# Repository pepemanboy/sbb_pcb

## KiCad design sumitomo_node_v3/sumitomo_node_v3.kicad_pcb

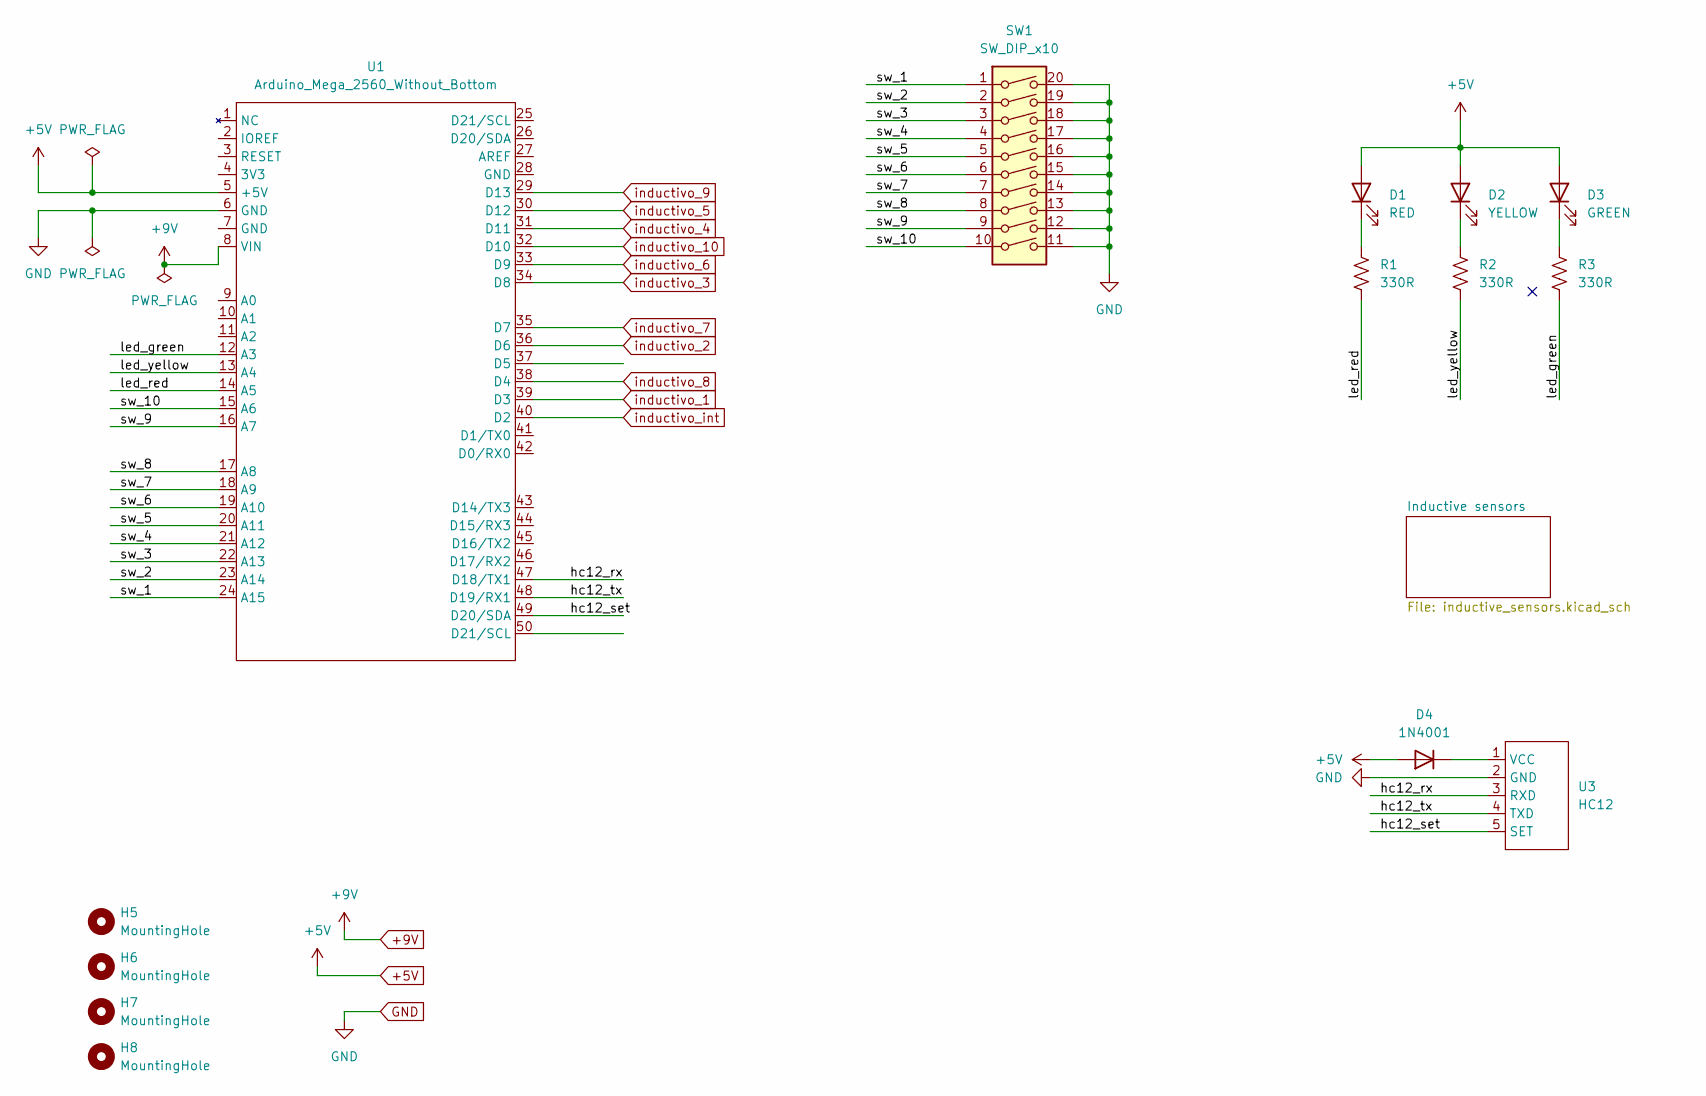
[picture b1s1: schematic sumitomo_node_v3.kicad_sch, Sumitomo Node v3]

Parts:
D1: RED; LED_D5.0mm
D2: YELLOW; LED_D5.0mm
D3: GREEN; LED_D5.0mm
D4: 1N4001; D_DO-41_SOD81_P10.16mm_Horizontal
H5, H6, H7, H8: MountingHole; MountingHole_3.2mm_M3_ISO7380
R1, R2, R3: 330R; R_Axial_DIN0207_L6.3mm_D2.5mm_P10.16mm_Horizontal
SW1: SW_DIP_x10; SW_DIP_SPSTx10_Slide_9.78x27.58mm_W7.62mm_P2.54mm
U1: Arduino_Mega_2560_Without_Bottom
U3: HC12; HC12_RF_Module

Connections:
+5V: D1.2 (A), D2.2 (A), D3.2 (A), D4.2 (A), U1.5 (+5V); also elsewhere on the board
+9V: U1.8 (VIN); also elsewhere on the board
/hc12_rx: U1.47 (D18/TX1), U3.3 (RXD)
/hc12_set: U1.49 (D20/SDA), U3.5 (SET)
/hc12_tx: U1.48 (D19/RX1), U3.4 (TXD)
/led_green: R3.1, U1.12 (A3)
/led_red: R1.1, U1.14 (A5)
/led_yellow: R2.1, U1.13 (A4)
/sw_1: SW1.1, U1.24 (A15)
/sw_2: SW1.2, U1.23 (A14)
/sw_3: SW1.3, U1.22 (A13)
/sw_4: SW1.4, U1.21 (A12)
/sw_5: SW1.5, U1.20 (A11)
/sw_6: SW1.6, U1.19 (A10)
/sw_7: SW1.7, U1.18 (A9)
/sw_8: SW1.8, U1.17 (A8)
/sw_9: SW1.9, U1.16 (A7)
/sw_10: SW1.10, U1.15 (A6)
GND: SW1.11, SW1.12, SW1.13, SW1.14, SW1.15, SW1.16, SW1.17, SW1.18, SW1.19, SW1.20, U1.6 (GND), U3.2 (GND); also elsewhere on the board
unnamed: D1.1 (K), R1.2
unnamed: D2.1 (K), R2.2
unnamed: D3.1 (K), R3.2
unnamed: D4.1 (K), U3.1 (VCC)
inductivo_1: U1.39 (D3); also elsewhere on the board
inductivo_2: U1.36 (D6); also elsewhere on the board
inductivo_3: U1.34 (D8); also elsewhere on the board
inductivo_4: U1.31 (D11); also elsewhere on the board
inductivo_5: U1.30 (D12); also elsewhere on the board
inductivo_6: U1.33 (D9); also elsewhere on the board
inductivo_7: U1.35 (D7); also elsewhere on the board
inductivo_8: U1.38 (D4); also elsewhere on the board
inductivo_9: U1.29 (D13); also elsewhere on the board
inductivo_10: U1.32 (D10); also elsewhere on the board
inductivo_int: U1.40 (D2); also elsewhere on the board

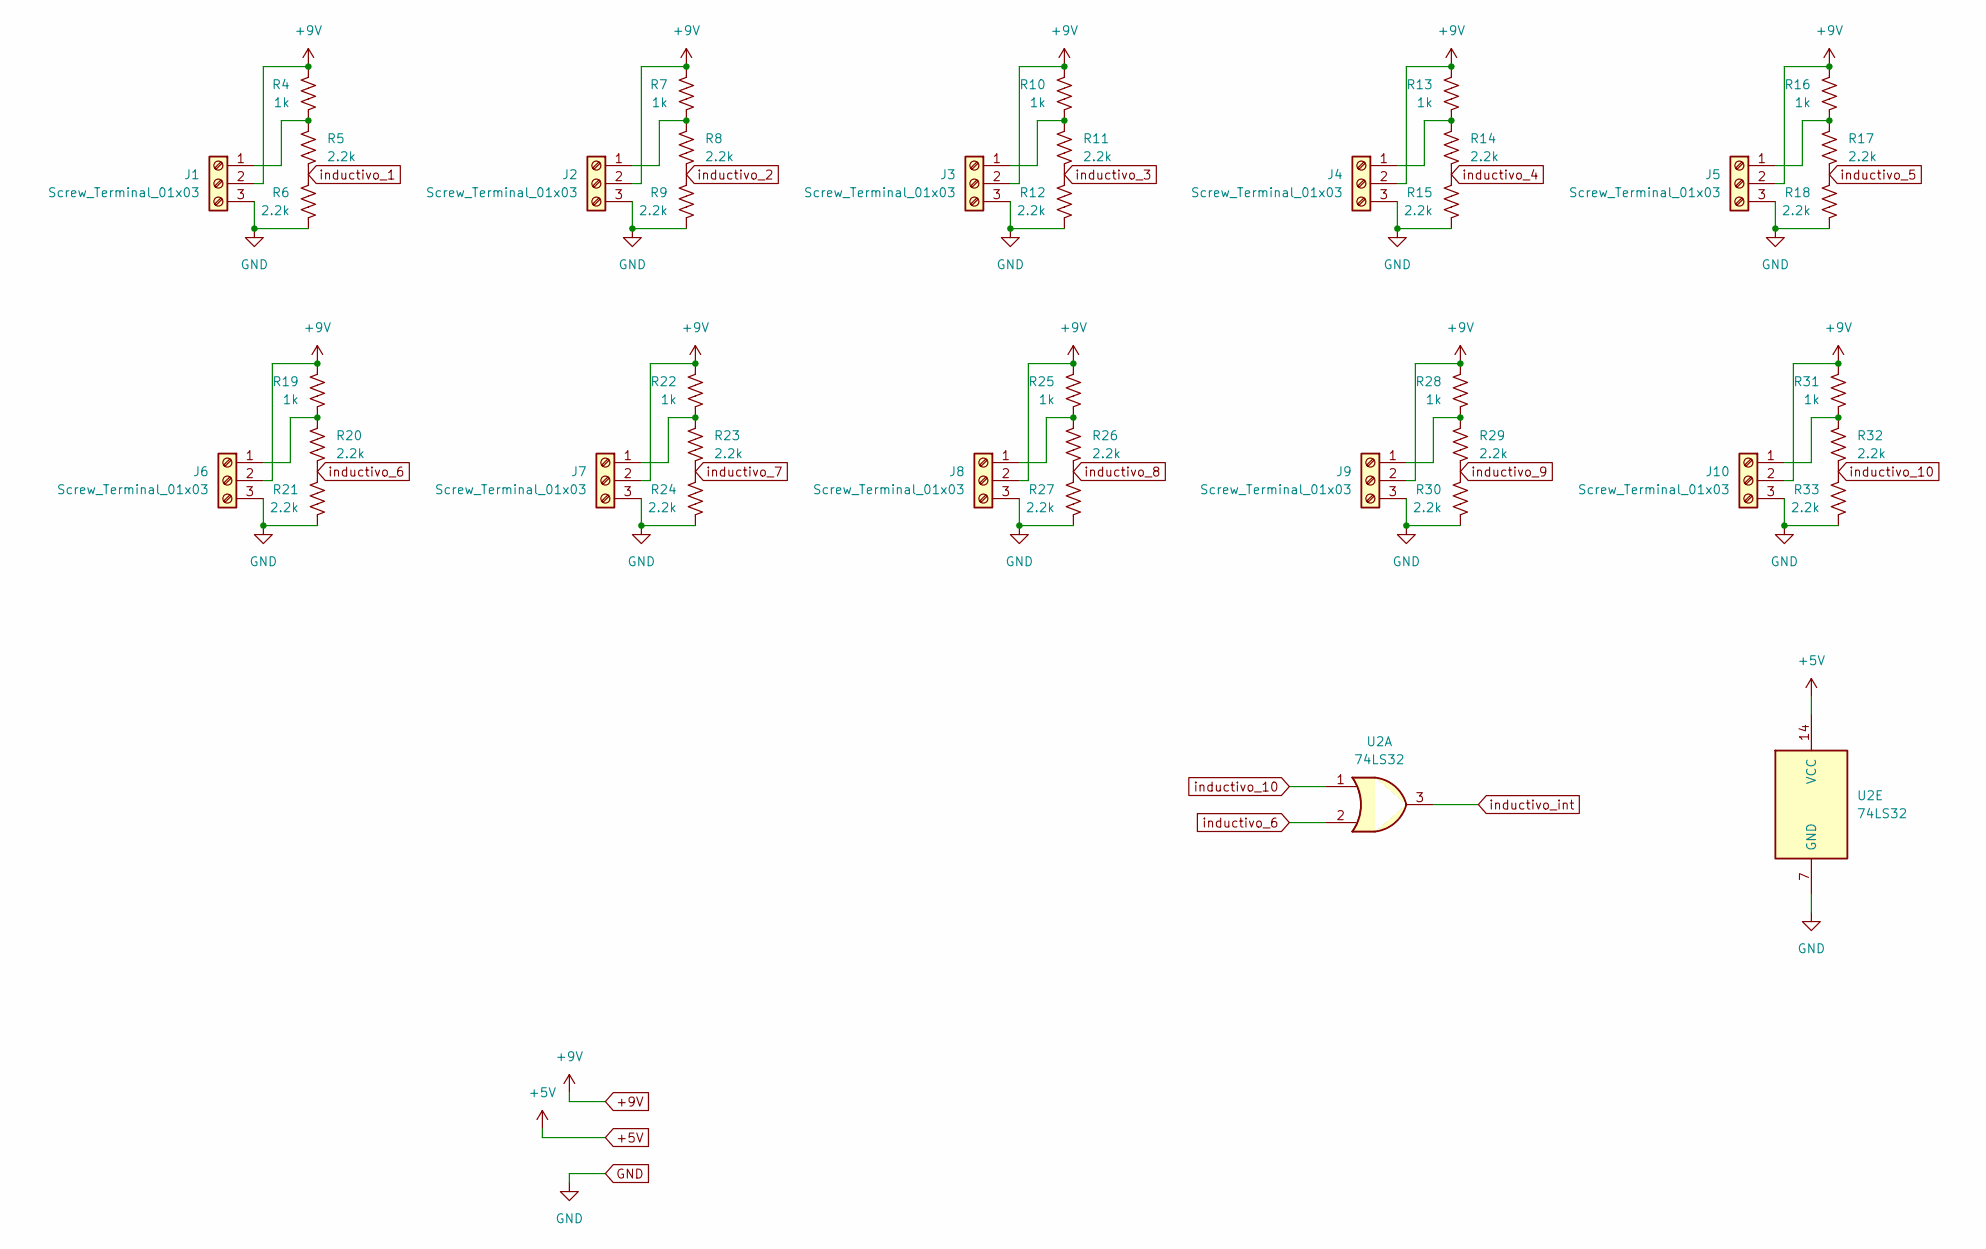
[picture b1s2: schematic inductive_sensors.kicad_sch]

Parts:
J1, J2, J3, J4, J5, J6, J7, J8, J9, J10: Screw_Terminal_01x03; Inductive_Sensor
R4, R7, R10, R13, R16, R19, R22, R25, R28, R31: 1k; R_Axial_DIN0207_L6.3mm_D2.5mm_P10.16mm_Horizontal
R5, R6, R8, R9, R11, R12, R14, R15, R17, R18, R20, R21, R23, R24, R26, R27, R29, R30, R32, R33: 2.2k; R_Axial_DIN0207_L6.3mm_D2.5mm_P10.16mm_Horizontal
U2: 74LS32; DIP-14_W7.62mm_LongPads

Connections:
+5V: U2.14 (VCC); also elsewhere on the board
+9V: J1.2, J2.2, J3.2, J4.2, J5.2, J6.2, J7.2, J8.2, J9.2, J10.2, R4.1, R7.1, R10.1, R13.1, R16.1, R19.1, R22.1, R25.1, R28.1, R31.1; also elsewhere on the board
GND: J1.3, J2.3, J3.3, J4.3, J5.3, J6.3, J7.3, J8.3, J9.3, J10.3, R6.1, R9.1, R12.1, R15.1, R18.1, R21.1, R24.1, R27.1, R30.1, R33.1, U2.7 (GND); also elsewhere on the board
unnamed: J1.1, R4.2, R5.1
unnamed: J2.1, R7.2, R8.1
unnamed: J3.1, R10.2, R11.1
unnamed: J4.1, R13.2, R14.1
unnamed: J5.1, R16.2, R17.1
unnamed: J6.1, R19.2, R20.1
unnamed: J7.1, R22.2, R23.1
unnamed: J8.1, R25.2, R26.1
unnamed: J9.1, R28.2, R29.1
unnamed: J10.1, R31.2, R32.1
inductivo_1: R5.2, R6.2; also elsewhere on the board
inductivo_2: R8.2, R9.2; also elsewhere on the board
inductivo_3: R11.2, R12.2; also elsewhere on the board
inductivo_4: R14.2, R15.2; also elsewhere on the board
inductivo_5: R17.2, R18.2; also elsewhere on the board
inductivo_6: R20.2, R21.2, U2.2; also elsewhere on the board
inductivo_7: R23.2, R24.2; also elsewhere on the board
inductivo_8: R26.2, R27.2; also elsewhere on the board
inductivo_9: R29.2, R30.2; also elsewhere on the board
inductivo_10: R32.2, R33.2, U2.1; also elsewhere on the board
inductivo_int: U2.3; also elsewhere on the board

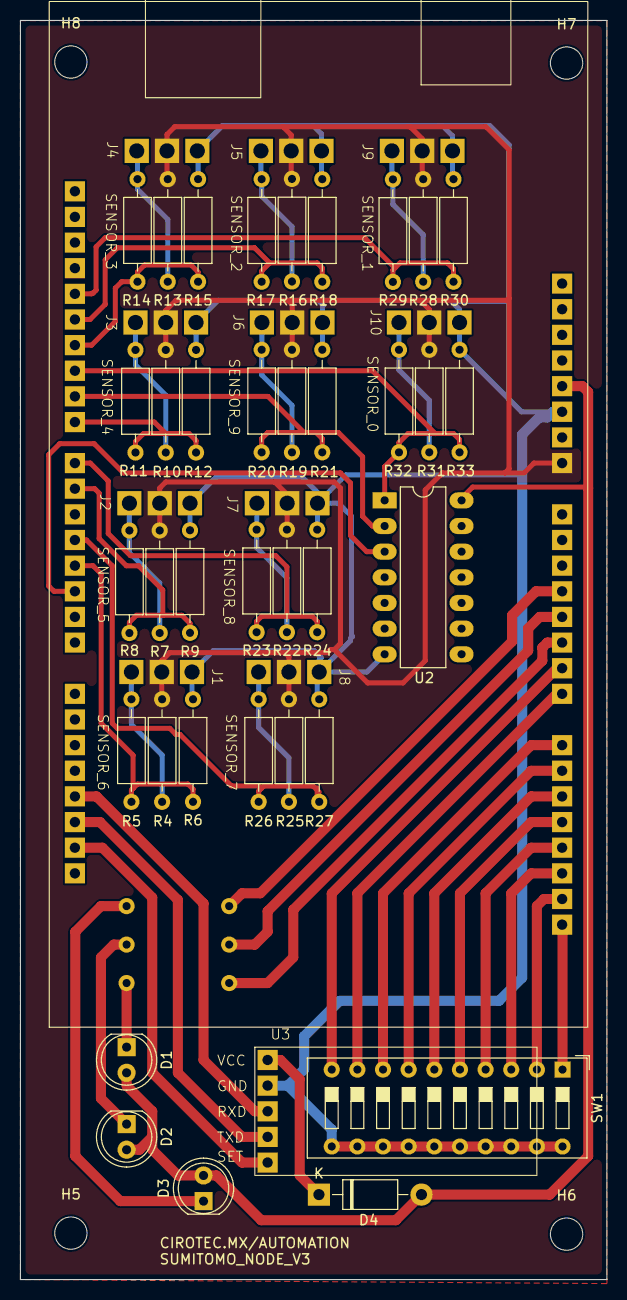
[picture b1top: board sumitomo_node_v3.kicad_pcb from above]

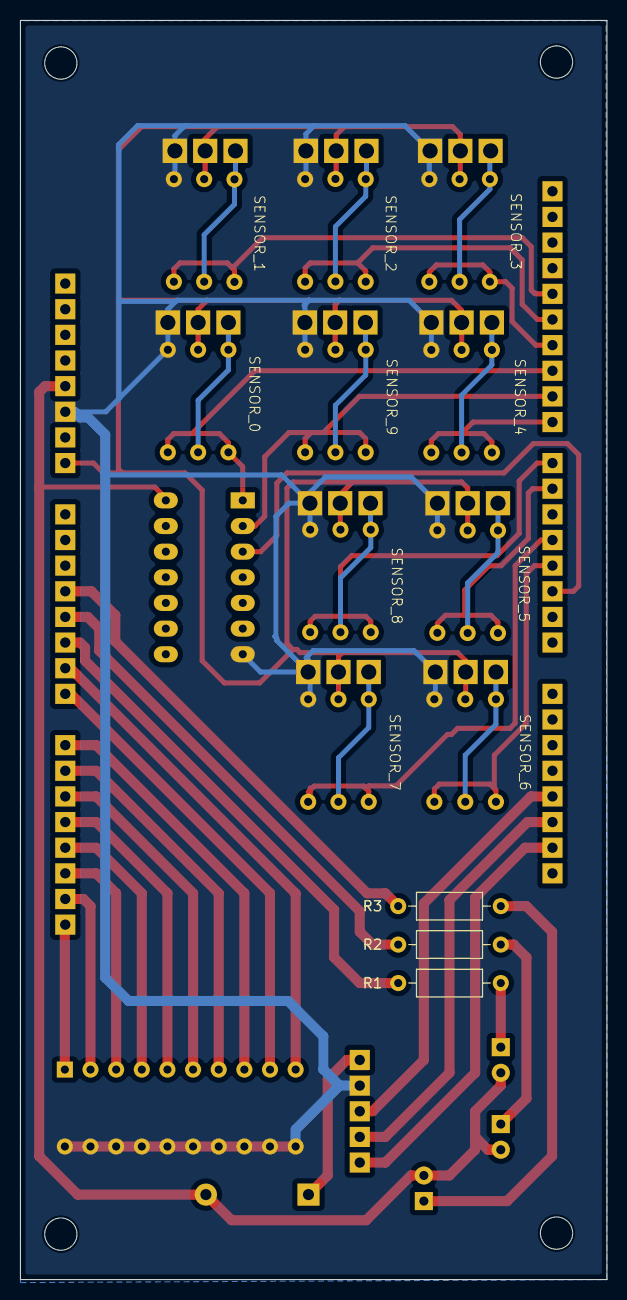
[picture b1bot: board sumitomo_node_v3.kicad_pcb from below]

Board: 2 copper layers, 58.1 x 124.7 mm, 55 parts (4 on the bottom side), 44 nets.

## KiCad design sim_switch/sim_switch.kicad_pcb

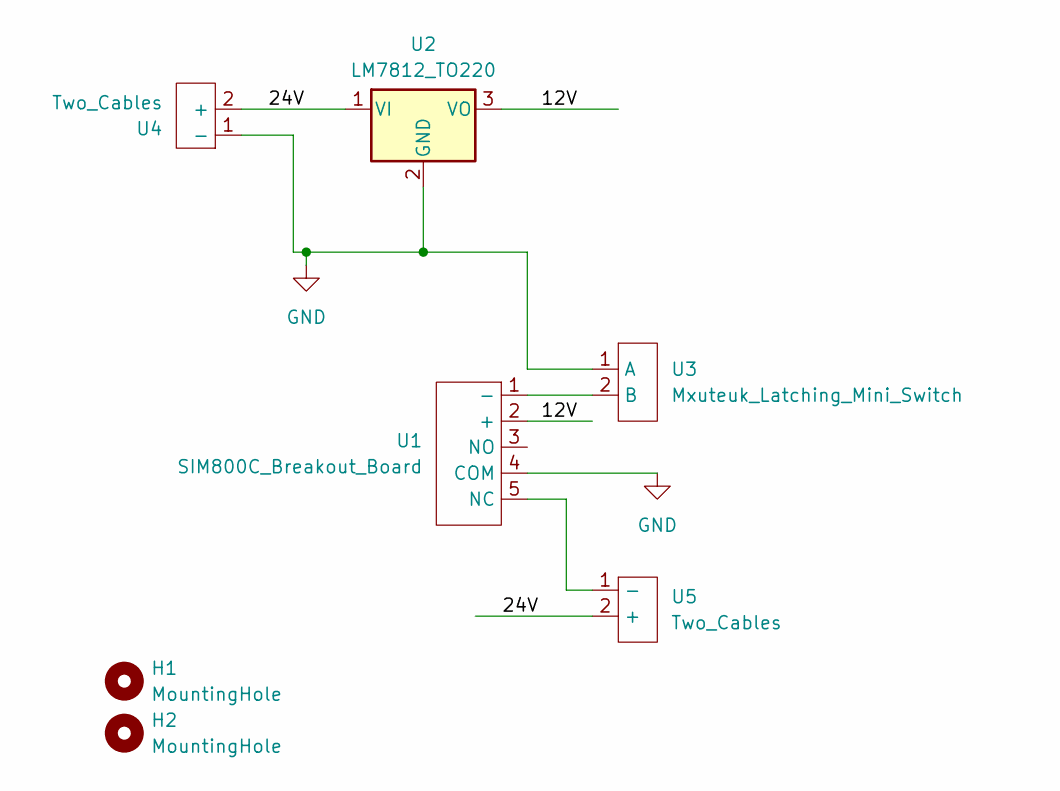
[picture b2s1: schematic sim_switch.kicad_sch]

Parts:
H1, H2: MountingHole; MountingHole_2.1mm
U1: SIM800C_Breakout_Board
U2: LM7812_TO220; TO-220-3_Vertical
U3: Mxuteuk_Latching_Mini_Switch
U4, U5: Two_Cables

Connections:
/12V: U1.2 (+), U2.3 (VO)
/24V: U2.1 (VI), U4.2 (+), U5.2 (+)
GND: U1.4 (COM), U2.2 (GND), U3.1 (A), U4.1 (-)
unnamed: U1.1 (-), U3.2 (B)
unnamed: U1.5 (NC), U5.1 (-)

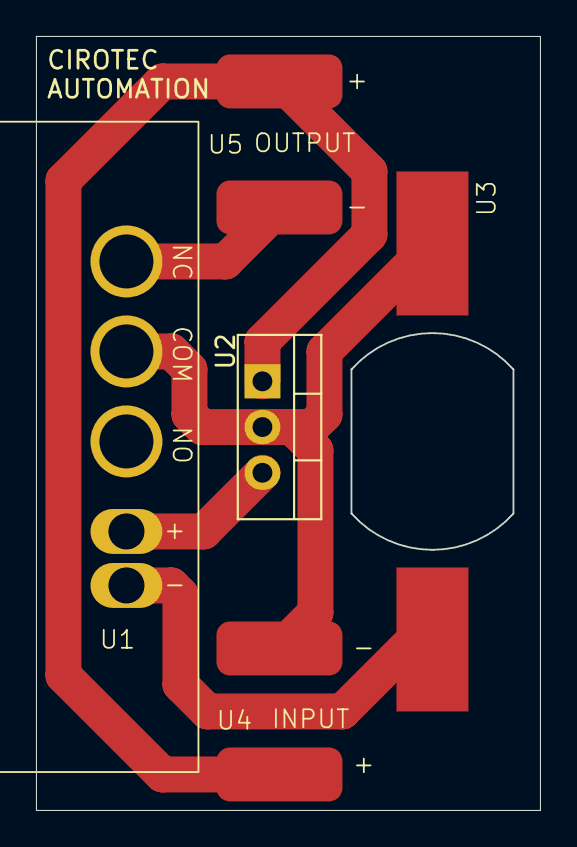
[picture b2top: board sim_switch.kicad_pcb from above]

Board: 2 copper layers, 27.9 x 43.0 mm, 7 parts (0 on the bottom side), 5 nets.

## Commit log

2024-03-19 Add `sumitomo_node_v2` files.
2024-03-19 Ignore unused KiCad files.
2024-03-19 Update library paths and unsaved changes to `sumitomo_node_v2`.
2024-03-19 Add svgs for `sumitomo_node_v2`.
2024-03-30 Fix PN532 UART and re-route to Serial2.
2024-03-30 Add rework instructions.
2024-05-25 Add Sim Switch project.
2024-09-26 Sim Switch project improvements
2024-10-21 Add Node v3 project.
2024-10-21 Add schematic in PDF for Node v3.
